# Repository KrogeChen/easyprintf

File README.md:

# easyprintf
easy printf debug box for small mcu

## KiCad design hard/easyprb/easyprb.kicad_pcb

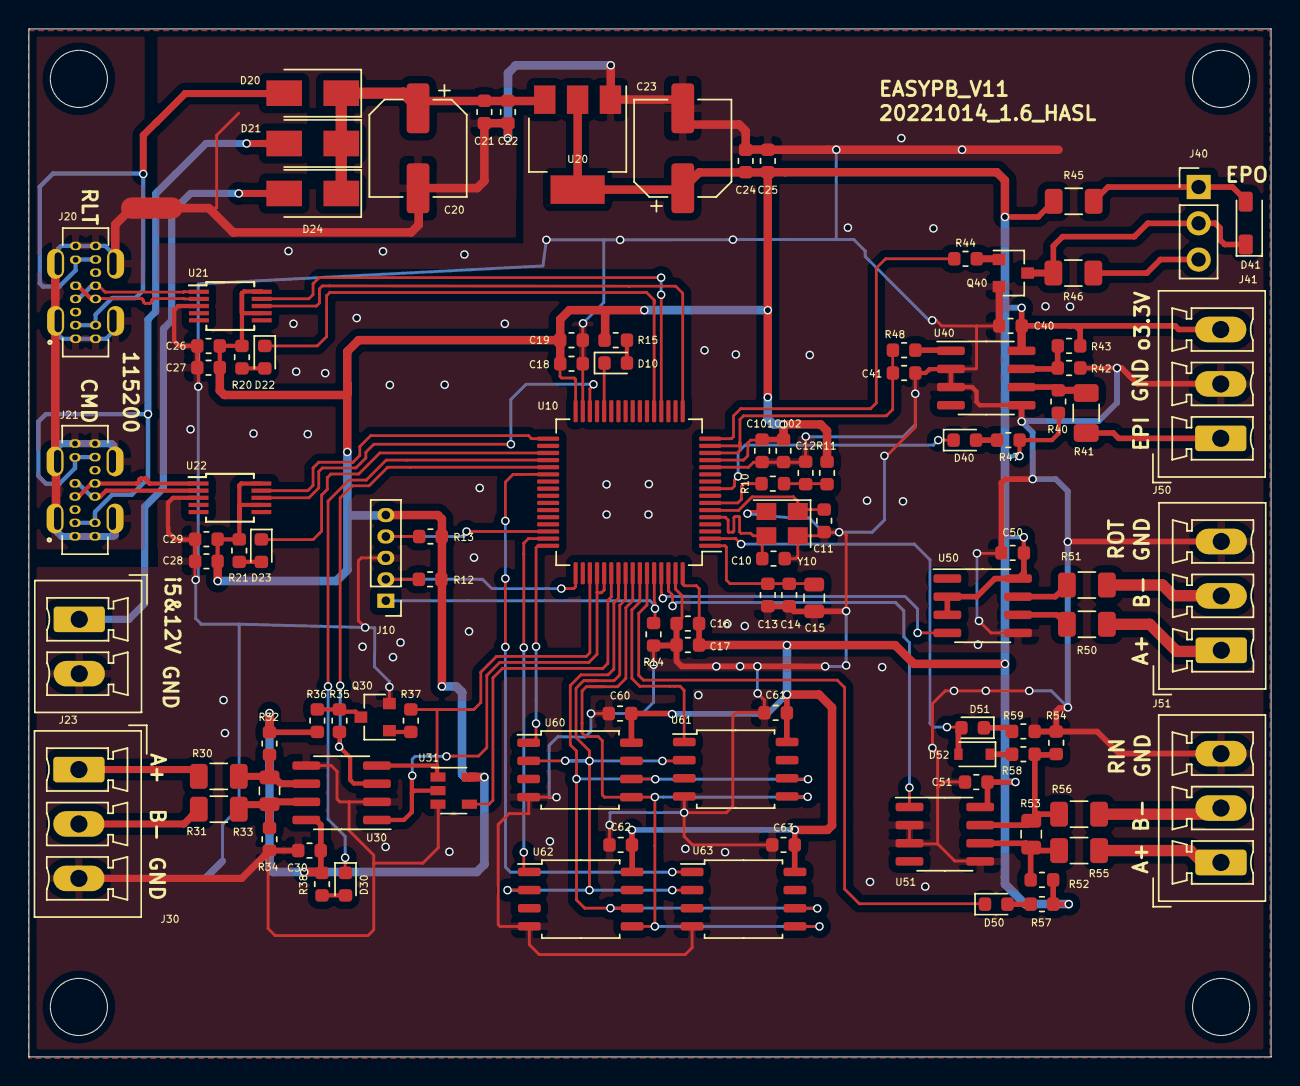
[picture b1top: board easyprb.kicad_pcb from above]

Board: 2 copper layers, 87.0 x 72.0 mm, 104 parts (0 on the bottom side), 74 nets.

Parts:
C10, C11: 9pF; C_0603_1608Metric
C12, C13, C17, C19, C22, C25, C27, C29, C30, C40, C50, C51, C60, C61, C62, C63, C102: 100nF; C_0603_1608Metric
C14, C21, C24, C26, C28: 1uF; C_0603_1608Metric
C15: 10uF; C_0805_2012Metric
C16, C18, C101: 4.7uF; C_0603_1608Metric
C20, C23: 220uF; CP_Elec_6.3x5.4
C41: 10nF; C_0603_1608Metric
D10, D22, D23: RED; LED_0603_1608Metric
D20, D21, D24: SS14; D_SMA
D30, D40, D50: GREEN; LED_0603_1608Metric
D41: RED; LED_4014
D51: BLUE; LED_0603_1608Metric
D52: 1N4148; D_SOD-323F
J10: DBG; PinHeader_1x05_P1.50mm_Vertical
J20: RLTC; USB_C_Receptacle_14Pin
J21: CMD; USB_C_Receptacle_14Pin
J23: PWU; PhoenixContact_MCV_1,5_2-G-3.81_1x02_P3.81mm_Vertical
J30: RS485; PhoenixContact_MCV_1,5_3-G-3.81_1x03_P3.81mm_Vertical
J40: EPO; PinHeader_1x03_P2.54mm_Vertical
J41: EPF; PhoenixContact_MCV_1,5_3-G-3.81_1x03_P3.81mm_Vertical
J50: TO RS; PhoenixContact_MCV_1,5_3-G-3.81_1x03_P3.81mm_Vertical
J51: UF RS485; PhoenixContact_MCV_1,5_3-G-3.81_1x03_P3.81mm_Vertical
Q30: S8050; SOT-23
Q40: 2N7002; SOT-23
R10, R44: 100R; R_0603_1608Metric
R11, R12, R13, R14, R43, R52, R54, R58: 10k; R_0603_1608Metric
R15, R20, R21, R38, R40, R47, R57, R59: 2.7k; R_0603_1608Metric
R30, R31, R41, R46, R50, R51, R55, R56: 10R; R_1206_3216Metric
R32, R34, R35, R36, R37: 4.7k; R_0603_1608Metric
R33: 470R; R_0805_2012Metric
R42: 6.8k; R_0603_1608Metric
R45: 180R; R_1206_3216Metric
R48: 51R; R_0603_1608Metric
R53: NP; R_0805_2012Metric
U10: HC32L136K8TA_LQFP64; LQFP-64_10x10mm_P0.5mm
U20: AMS1117-3.3; SOT-223
U21, U22: CH340E; MSOP-10_3x3mm_P0.5mm
U30, U40, U50, U51: SP3485EN; SOIC-8_3.9x4.9mm_P1.27mm
U31: 74LVC1G86; SOT-23-5
U60, U61, U62, U63: W25Q128JVS; SOIC-8_5.23x5.23mm_P1.27mm
Y10: 16M; Crystal_SMD_3225-4Pin_3.2x2.5mm

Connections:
/A1: J30.1, R30.2
/A2: J50.1, R50.1
/A3: J51.1, R55.1
/B1: J30.2, R31.2
/B2: J50.2, R51.1
/B3: J51.2, R56.1
/BOOT: J10.1, R14.1, U10.60
/CFT: U10.54, U31.4
/CS0: U10.48, U60.1
/CS1: U10.58, U61.1
/CS2: U10.47, U62.1
/CS3: U10.38, U63.1
/D1+: J20.A6, J20.B6, U21.1
/D1-: J20.A7, J20.B7, U21.2
/D2+: J21.A6, J21.B6, U22.1
/D2-: J21.A7, J21.B7, U22.2
/EPF: R44.2, U10.16
/EPI: J41.1, R41.1
/EPN: C41.2, R48.2, U10.14, U10.15
/EPO: D41.1, J40.2, Q40.3, R46.2
/LE0: D22.1, U10.21
/LE1: D23.1, U10.35
/LE2: D30.1, U10.36
/LE3: D50.1, U10.59
/LE4: D40.1, U10.9
/LEM: D10.1, U10.28
/LRX0: U10.30, U22.8
/LRX1: U10.52, U10.53, U30.1, U31.2
/LTX0: U10.33, U22.9
/LTX1: R37.1, U10.51, U30.4, U31.1
/MISO: U10.56, U60.2, U61.2, U62.2, U63.2
/MOSI: U10.57, U60.5, U61.5, U62.5, U63.5
/RST: R10.2, U10.7
/RX0: U10.62, U51.1
/RX1: U10.17, U21.8
/SCLK: U10.55, U60.6, U61.6, U62.6, U63.6
/SWC: J10.2, R12.2, U10.49
/SWD: J10.4, R13.2, U10.46
/TEN: R35.2, U10.37, U30.3
/TLL: D51.2, D52.2, U10.2
/TX0: U10.61, U50.4
/TX1: U10.20, U21.9
/VUA: D20.2, J20.A4, J20.A9, J20.B4, J20.B9
/VUB: D21.2, J21.A4, J21.A9, J21.B4, J21.B9
/VUC: D24.2, J23.1
/Y_N: C10.1, U10.5, Y10.3
/Y_P: C11.1, U10.6, Y10.1
GND: C10.2, C11.2, C12.2, C13.1, C14.1, C15.1, C16.1, C17.1, C18.2, C19.2, C20.2, C21.2, C22.2, C23.2, C24.2, C25.2, C26.2, C27.2, C28.2, C29.2, C30.1, C40.1, C41.1, C50.1, C51.1, C60.1, C61.1, C62.1, C63.1, C101.1, C102.1, J10.3, J20.A1, J20.A12, J20.B1, J20.B12, J20.S1, J20.S2, J20.S3, J20.S4, J21.A1, J21.A12, J21.B1, J21.B12, J21.S1, J21.S2, J21.S3, J21.S4, J23.2, J30.3, J41.2, J50.3, J51.3, Q30.2, Q40.2, R14.2, R34.2, R42.1, R54.1, R59.1, U10.12, U10.31, U10.63, U20.1, U21.3, U22.3, U30.2, U30.5, U31.3, U40.2, U40.3, U40.5, U50.5, U51.2, U51.3, U51.5, U60.4, U61.4, U62.4, U63.4, Y10.2, Y10.4
unnamed: C12.1, R10.1, R11.2
unnamed: C13.2, C14.2, C15.2, U10.1
unnamed: C20.1, C21.1, C22.1, D20.1, D21.1, D24.1, U20.3
unnamed: D10.2, R15.1
unnamed: D22.2, R20.1
unnamed: D23.2, R21.1
unnamed: D30.2, R38.1
unnamed: D40.2, R47.1
unnamed: D41.2, J40.1, R45.2
unnamed: D50.2, R57.1
unnamed: D51.1, R59.2
unnamed: D52.1, R58.1
unnamed: J40.3, R46.1
unnamed: Q30.1, R37.2
unnamed: Q30.3, R35.1, R36.2
unnamed: Q40.1, R44.1
unnamed: R30.1, R32.2, R33.2, U30.6
unnamed: R31.1, R33.1, R34.1, U30.7
unnamed: R40.2, R41.2, U40.6
unnamed: R42.2, R43.1, U40.7
unnamed: R48.1, U40.1
unnamed: R50.2, U50.6
unnamed: R51.2, U50.7
unnamed: R52.1, R53.2, R55.2, U51.6
unnamed: R53.1, R54.2, R56.2, R58.2, U51.7
VCC: C16.2, C17.2, C18.1, C19.1, C23.1, C24.1, C25.1, C26.1, C27.1, C28.1, C29.1, C30.2, C40.2, C50.2, C51.2, C60.2, C61.2, C62.2, C63.2, C101.2, C102.2, J10.5, J41.3, R11.1, R12.1, R13.1, R15.2, R20.2, R21.2, R32.1, R36.1, R38.2, R40.1, R43.2, R45.1, R47.2, R52.2, R57.2, U10.13, U10.32, U10.64, U20.2, U20.4, U21.7, U21.10, U22.7, U22.10, U30.8, U31.5, U40.8, U50.2, U50.3, U50.8, U51.8, U60.8, U61.8, U62.8, U63.8

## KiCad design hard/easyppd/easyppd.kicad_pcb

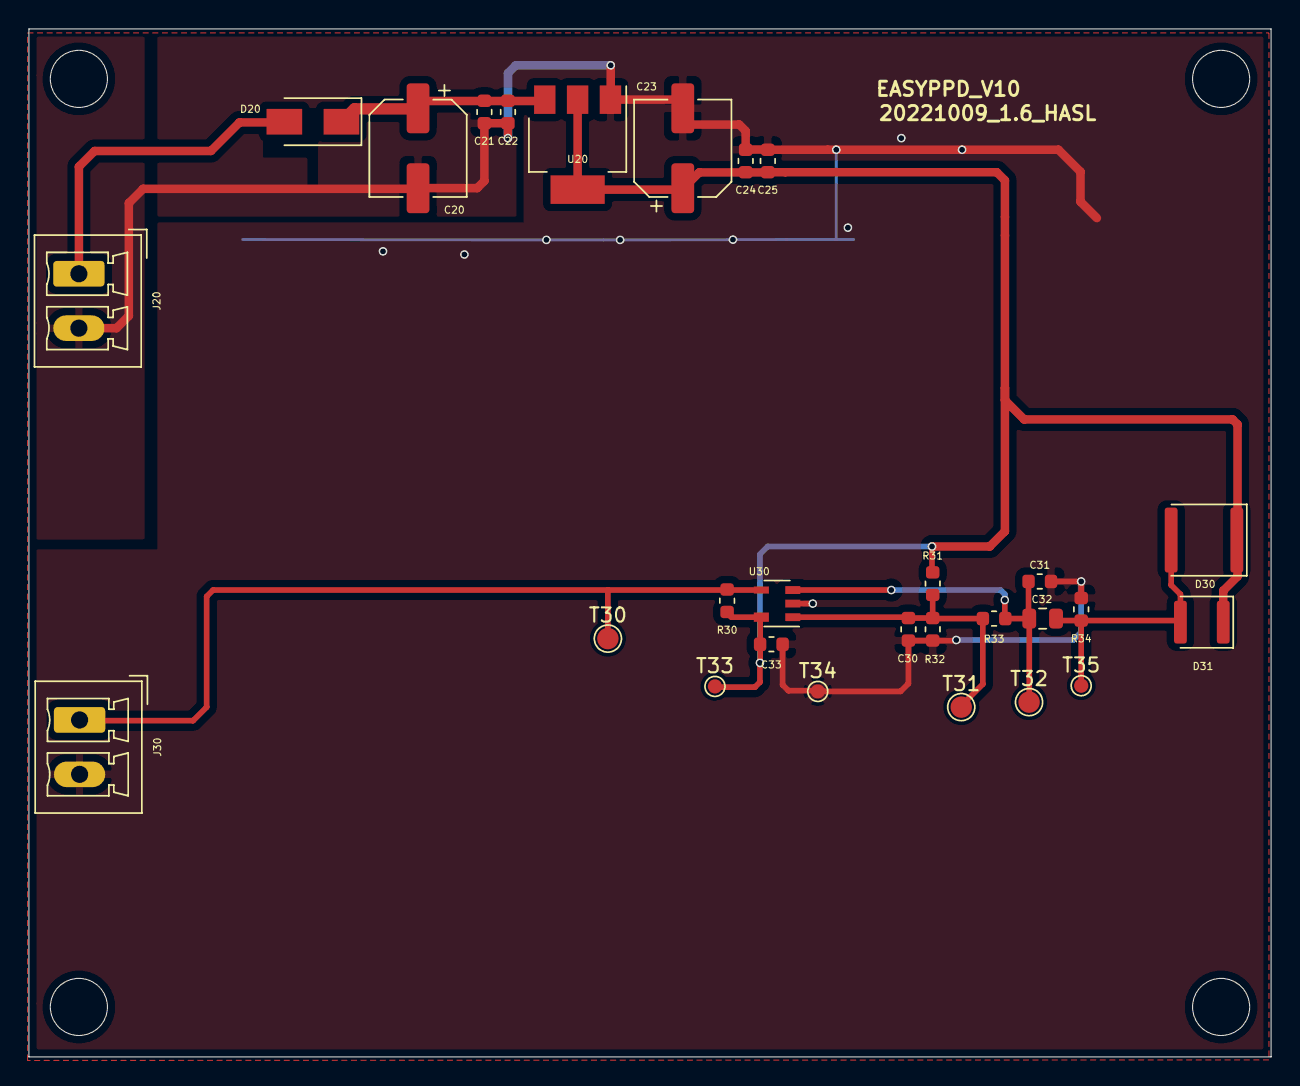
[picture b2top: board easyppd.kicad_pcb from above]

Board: 2 copper layers, 87.0 x 72.0 mm, 28 parts (0 on the bottom side), 8 nets.

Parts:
C20, C23: 220uF; CP_Elec_6.3x5.4
C21, C24, C33: 1uF; C_0603_1608Metric
C22, C25, C30: 100nF; C_0603_1608Metric
C31: np; C_0603_1608Metric
C32: 10uF; C_0805_2012Metric
D20: SS14; D_SMA
D30: PD; LED_TM5080
D31: PD; LED_PD2833
J20: POWER; PhoenixContact_MCV_1,5_2-G-3.81_1x02_P3.81mm_Vertical
J30: OUT; PhoenixContact_MCV_1,5_2-G-3.81_1x02_P3.81mm_Vertical
R30, R31, R32, R34: 10k; R_0603_1608Metric
R33: 220k; R_0603_1608Metric
T30, T31, T32: TP; TestPoint_Pad_D1.5mm
T33, T34, T35: TP; TestPoint_Pad_D1.0mm
U20: AMS1117-3.3; SOT-223
U30: LMV331; SOT-23-5

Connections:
/VUA: D20.2, J20.1
GND: C20.2, C21.2, C22.2, C23.2, C24.2, C25.2, C30.1, C31.1, C33.1, J20.2, J30.2, R32.2, R34.2, T34.1, U20.1, U30.2
unnamed: C20.1, C21.1, C22.1, D20.1, U20.3
unnamed: C30.2, R31.2, R32.1, R33.2, T31.1, U30.1
unnamed: C31.2, C32.1, R33.1, T32.1, U30.3
unnamed: C32.2, D30.2, D31.2, R34.1, T35.1
unnamed: J30.1, R30.2, T30.1, U30.4
VCC: C23.1, C24.1, C25.1, C33.2, D30.1, D31.1, R30.1, R31.1, T33.1, U20.2, U20.4, U30.5

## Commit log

2022-09-11 start this design
2022-09-13 sch design is working
2022-09-14 easy print box sch is complete
2022-09-16 hardware is complete. it is does manufacture.
2022-09-21 Create the framework code in this project
2022-09-21 pilot light is complete
2022-09-21 epf transmit wave's code is ok
2022-09-22 epf accept decode program is complete
2022-09-23 epf data transfer to uart is debug complete.
2022-09-23 add some project files
2022-09-23 add a soft folder README file
2022-09-23 add epf message files
2022-09-23 add some notes
2022-09-23 some warning is dead
2022-09-23 add EPF_LOG_EN flag
2022-09-28 boot load function is works complete
2022-09-28 add hardware flag location in array
2022-09-29 add boot load feature and debug complete
2022-10-01 storage small module support bit 16 W size. firmware legal verify add hardware flag check.
2022-10-02 improve some notes
2022-10-04 BOOT and mbus link debug complete
2022-10-14 增加关电读头的电路
2022-10-14 增加端子电源接口，EPF输入接口增加VCC，方便连接光电数据头
2022-10-14 修正USB封装，使焊接更加容易。
2022-10-17 modify easy prb，epo change to led type interface
2022-10-17 crystal user differential pair
2022-10-17 add usb differential pair
